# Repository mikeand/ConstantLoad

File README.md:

# ConstantLoad
KiCad project for opamp constant current load for battery testing

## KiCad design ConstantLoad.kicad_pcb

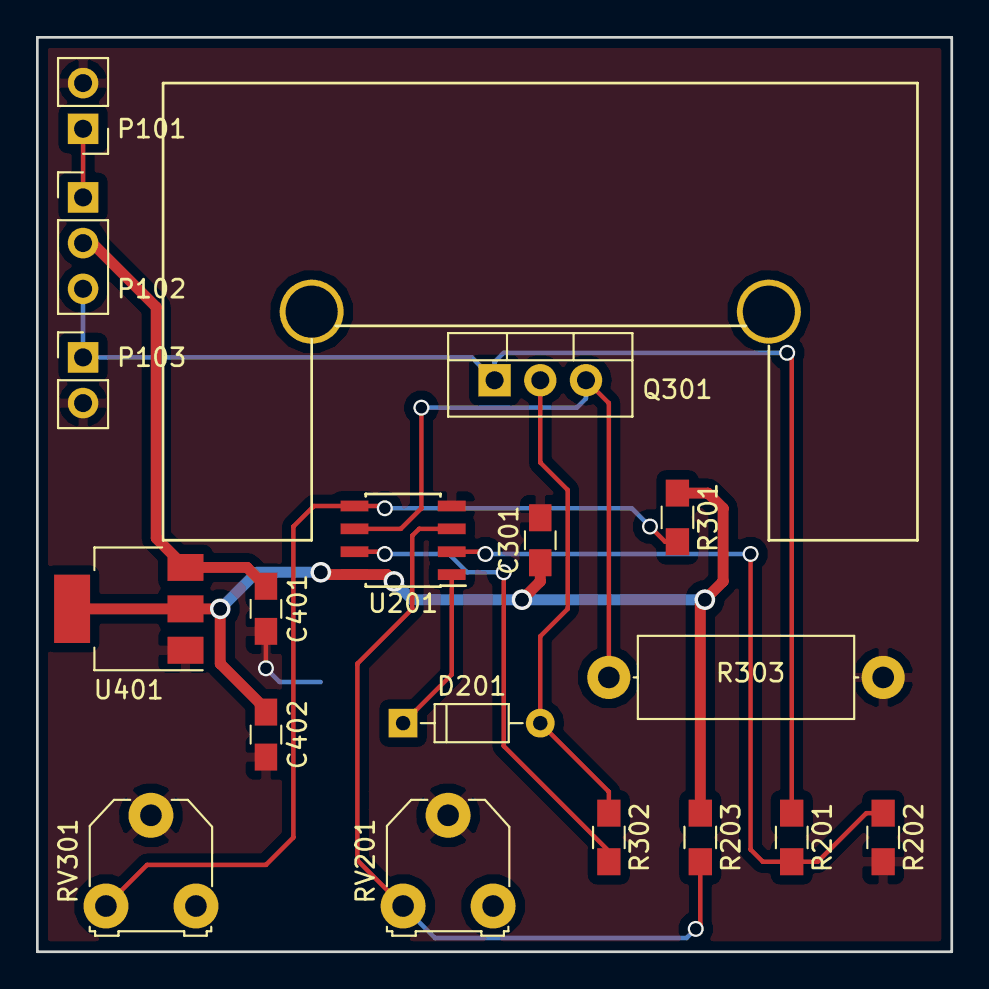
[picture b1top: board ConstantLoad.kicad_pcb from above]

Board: 2 copper layers, 50.8 x 50.8 mm, 18 parts (0 on the bottom side), 12 nets.

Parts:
C301, C401: C; C_0805_HandSoldering
C402: 22U; C_0805_HandSoldering
D201: D; D_DO-35_SOD27_P7.62mm_Horizontal
P101: Battery Input; Pin_Header_Straight_1x02_Pitch2.54mm
P102: Jumper; Pin_Header_Straight_1x03_Pitch2.54mm
P103: Current Sink Input; Pin_Header_Straight_1x02_Pitch2.54mm
Q301: IRL640A; TO-220_Vertical
R201: 9K; R_0805_HandSoldering
R202, R302: 1K; R_0805_HandSoldering
R203: 27K; R_0805_HandSoldering
R301: 68K; R_0805_HandSoldering
R303: .1; R_Axial_DIN0414_L11.9mm_D4.5mm_P15.24mm_Horizontal
RV201, RV301: 10K; Potentiometer_Triwood_RM-065
U201: LMV358; SOIC-8_3.9x4.9mm_Pitch1.27mm
U401: AMS1117; SOT-223-3Lead_TabPin2

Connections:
3.3V: C301.1, C402.1, R203.1, R301.1, U201.8, U401.2
/Current Control/Current_Sink_In: P102.3, P103.1, Q301.1, R201.1
/Current Control/FET_Gate: D201.2, Q301.2, R302.1
/Power Regulation/Vin: C401.1, P102.2, U401.3
GND: C301.2, C401.2, C402.2, P101.2, P103.2, R202.2, R303.2, RV201.2, RV301.2, U201.4, U401.1
unnamed: D201.1, U201.1
unnamed: P101.1, P102.1
unnamed: Q301.3, R303.1, U201.6
unnamed: R201.2, R202.1, U201.2
unnamed: R203.2, RV201.1, U201.3
unnamed: R301.2, RV301.1, U201.5
unnamed: R302.2, U201.7

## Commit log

2017-02-24 KiCad project creation
2017-02-25 Add basic schematic
2017-02-26 Add part numbers
2017-02-27 Break up circuit into sheets
2017-02-27 Update project
2017-02-27 Add annotations
2017-02-27 Associated parts with layout
2017-02-28 Add heatsink to PCB
2017-02-28 Do pcb layout
2017-03-01 Added logo
2017-03-01 Generate Gerbers
